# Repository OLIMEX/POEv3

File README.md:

# POEv3
Power Over Ethernet 802.03af compatible non isolated power supply module

## License
* Hardware is released under Apache 2.0 License
* Software is released under GPL3 License
* Documentation is released under CC BY-SA 3.0

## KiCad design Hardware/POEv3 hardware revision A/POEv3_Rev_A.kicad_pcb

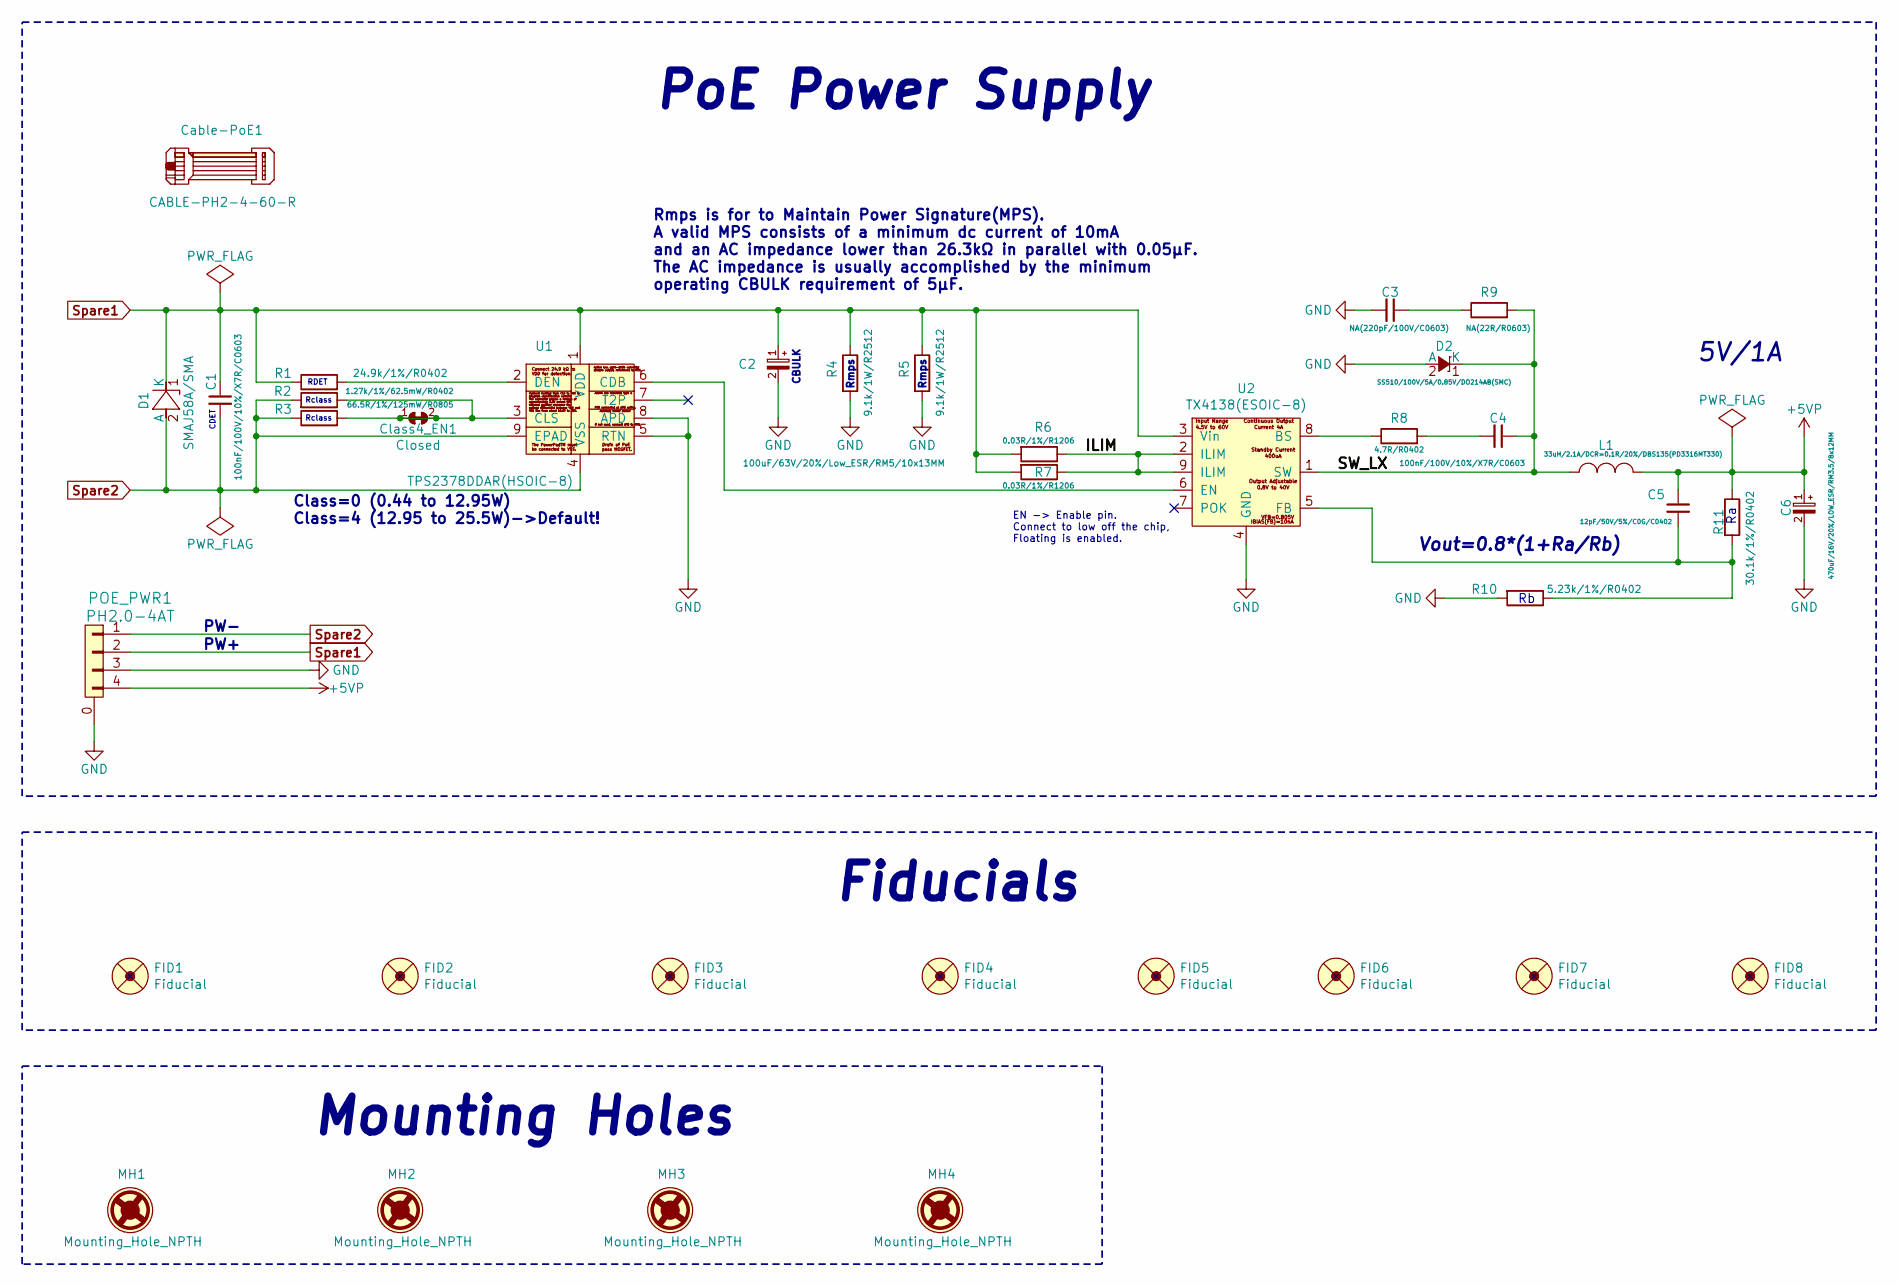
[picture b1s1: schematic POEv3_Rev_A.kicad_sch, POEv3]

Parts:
C1, C4: 100nF/100V/10%/X7R/C0603; C_0603_5MIL_DWS
C2: 100uF/63V/20%/Low_ESR/RM5/10x13MM; CPOL-RM5mm_10.0x16.0mm_PTH
C3: NA(220pF/100V/C0603); C_0603_5MIL_DWS
C5: 12pF/50V/5%/C0G/C0402; C_0402_5MIL_DWS
C6: 470uF/16V/20%/LOW_ESR/RM3.5/8x12MM; CPOL-RM3.5mm_8.0x11.5mm_PTH
Cable-PoE1: CABLE-PH2-4-60-R; Cable-IDC
Class4_EN1: Closed; SJ_Closed
D1: SMAJ58A/SMA; SMA-KA
D2: SS510/100V/5A/0.85V/DO214AB(SMC); DO214AB(SMC)_1(K)-2(A)
FID1, FID2, FID5, FID6: Fiducial; Fiducial1x3
FID3, FID4, FID7, FID8: Fiducial; Fiducial1x3_Paste
L1: 33uH/2.1A/DCR=0.1R/20%/DBS135(PD3316MT330); HSMRH129_12.0x12.5x9.5(max)
MH1, MH2, MH3, MH4: Mounting_Hole_NPTH; Mounting_Hole_Drill-3.3mm_Clerance-7mm
POE_PWR1: PH2.0-4AT; PH2.0-4PLB
R1: 24.9k/1%/R0402; R_0402_5MIL_DWS
R2: 1.27k/1%/62.5mW/R0402; R_0402_5MIL_DWS
R3: 66.5R/1%/125mW/R0805; R_0805_5MIL_DWS
R4, R5: 9.1k/1W/R2512; R_2512_MM_DWS
R6, R7: 0.03R/1%/R1206; R_1206_5MIL_DWS
R8: 4.7R/R0402; R_0402_5MIL_DWS
R9: NA(22R/R0603); R_0603_5MIL_DWS
R10: 5.23k/1%/R0402; R_0402_5MIL_DWS
R11: 30.1k/1%/R0402; R_0402_5MIL_DWS
U1: TPS2378DDAR(HSOIC-8); ESOIC-8
U2: TX4138(ESOIC-8); ESOIC-8

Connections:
+5VP: C5.1, C6.1 (+), L1.2, POE_PWR1.4 (P2), R11.1
/ILIM: R6.1, R7.1, U2.2 (ILIM), U2.9 (ILIM)
/SW_LX: C4.1, D2.1 (K), L1.1, R9.2, U2.1 (SW)
GND: C2.2 (-), C3.2, C6.2 (-), D2.2 (A), POE_PWR1.0, POE_PWR1.3 (P2), R4.2, R5.2, R10.2, U1.5 (RTN), U1.8 (APD), U2.4 (GND)
unnamed: C3.1, R9.1
unnamed: C4.2, R8.2
unnamed: U1.6 (CDB), U2.6 (EN)
unnamed: Class4_EN1.1, Class4_EN1.2, R2.1, R3.2, U1.3 (CLS)
unnamed: R1.2, U1.2 (DEN)
unnamed: R8.1, U2.8 (BS)
unnamed: C5.2, R10.1, R11.2, U2.5 (FB)
Spare1: C1.1, C2.1 (+), D1.1 (K), POE_PWR1.2, R1.1, R4.1, R5.1, R6.2, R7.2, U1.1 (VDD), U2.3 (Vin)
Spare2: C1.2, D1.2 (A), POE_PWR1.1, R2.2, R3.1, U1.4 (VSS), U1.9 (EPAD)

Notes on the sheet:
PW+
Vout=0.8*(1+Ra/Rb)
Rmps
RDET
Class=0 (0.44 to 12.95W) Class=4 (12.95 to 25.5W)->Default!
Rclass
5V/1A
CDET
Rmps is for to Maintain Power Signature(MPS). A valid MPS consists of a minimum dc current of 10mA and an AC impedance lower than 26.3kΩ in parallel with 0.05μF. The AC impedance is usually accomplished by the minimum operating CBULK requirement of 5μF.
CBULK
PW-
EN -> Enable pin. Connect to low off the chip, Floating is enabled.
Fiducials
Mounting Holes
PoE Power Supply

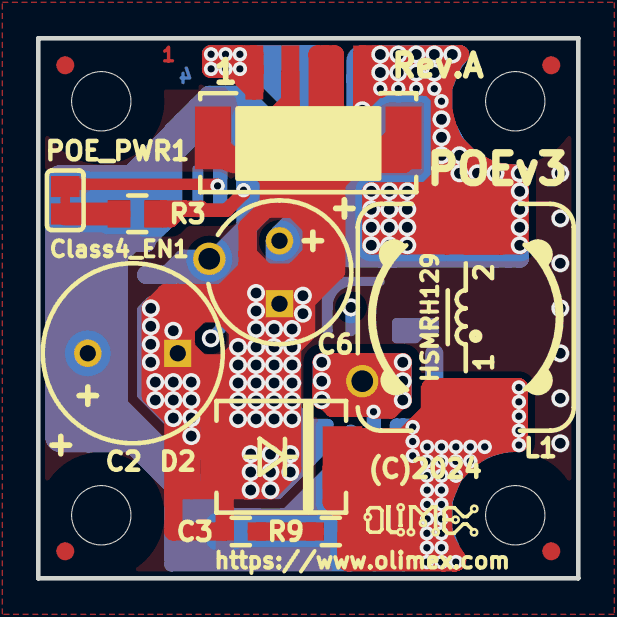
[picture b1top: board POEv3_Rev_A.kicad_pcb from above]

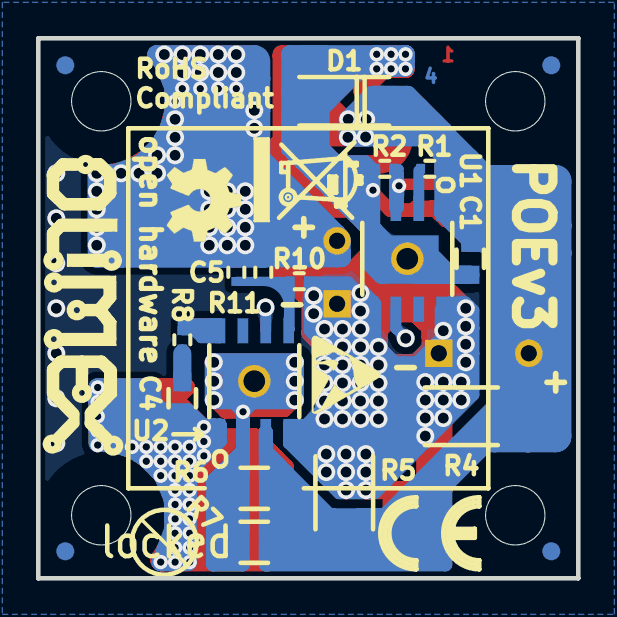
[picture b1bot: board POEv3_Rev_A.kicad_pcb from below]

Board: 4 copper layers, 30.0 x 30.0 mm, 44 parts (25 on the bottom side), 13 nets.

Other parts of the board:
Logo_OLIMEX_SMALL_TB: Logo_OLIMEX_SMALL_TB
Logo_OLIMEX_TB: Logo_OLIMEX_TB
Sign_Antistatic_150: Sign_Antistatic_150
Sign_CE: CE_Sign
Sign_OSHW_7.3x6.0mm: Sign_OSHW_7.3x6.0mm; Sign_OSHW_7.3x6.0mmn
Sign_PB-Free: Sign_PB-Free
Sign_RecycleBin_1: Sign_RecycleBin_1

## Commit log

2025-03-14 Update
    Added design files
2025-03-31 add user manual

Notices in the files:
Hardware/POEv3 hardware revision A/POEv3_Rev_A.kicad_pcb:
(C)2024
